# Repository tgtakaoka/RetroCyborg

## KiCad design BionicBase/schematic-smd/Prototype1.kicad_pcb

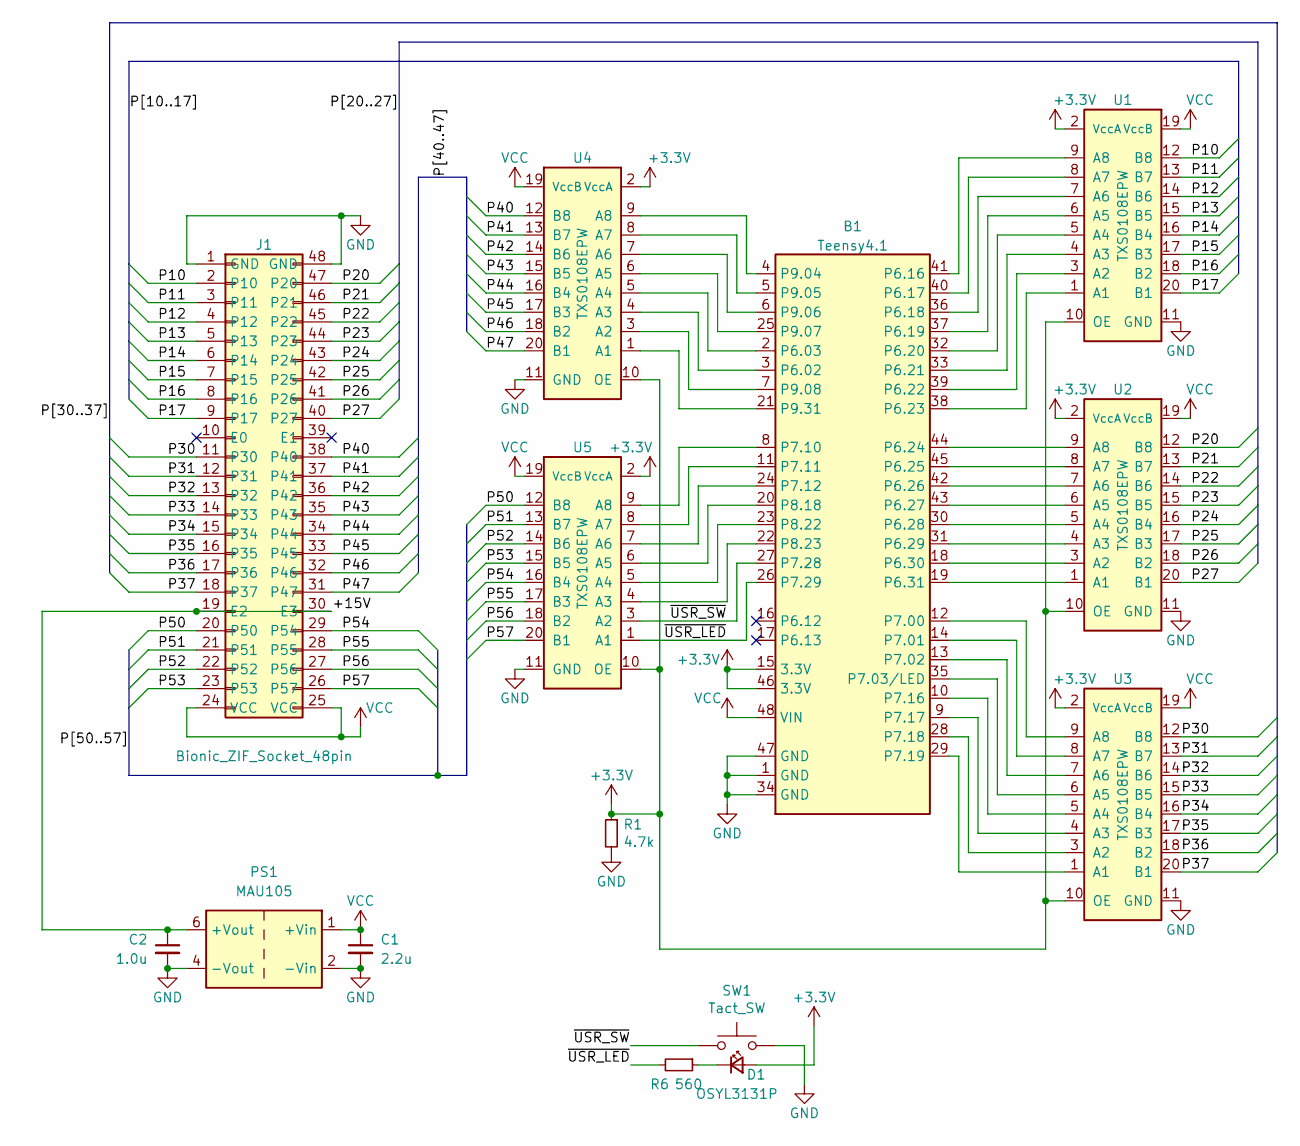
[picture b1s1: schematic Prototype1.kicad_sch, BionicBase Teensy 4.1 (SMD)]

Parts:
B1: Teensy4.1; DIP-48_W15.24mm
C1: 2.2u; C_0603_1608Metric_Pad1.08x0.95mm_HandSolder
C2: 1.0u; C_0603_1608Metric_Pad1.08x0.95mm_HandSolder
D1: OSYL3131P; LED_D3.0mm
J1: Bionic_ZIF_Socket_48pin; Aries_ZIF_socket_DIP-48-pin
PS1: MAU105; Converter_DCDC_Minmax_MAU100_THT
R1: 4.7k; R_Axial_DIN0204_L3.6mm_D1.6mm_P5.08mm_Horizontal
R6: 560; R_Axial_DIN0204_L3.6mm_D1.6mm_P5.08mm_Horizontal
SW1: Tact_SW; Tact_SW_6x6mm
U1, U2, U3, U4, U5: TXS0108EPW; TSSOP-20_4.4x6.5mm_P0.65mm

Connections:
+3.3V: B1.15 (3.3V), B1.46 (3.3V), D1.2 (A), R1.1, U1.2 (VccA), U1.10 (OE), U2.2 (VccA), U2.10 (OE), U3.2 (VccA), U3.10 (OE), U4.2 (VccA), U4.10 (OE), U5.2 (VccA), U5.10 (OE)
/+15V: C2.1, J1.19 (E2), J1.30 (E3), PS1.6 (+Vout)
/P10: J1.2 (P10), U1.12 (B8)
/P11: J1.3 (P11), U1.13 (B7)
/P12: J1.4 (P12), U1.14 (B6)
/P13: J1.5 (P13), U1.15 (B5)
/P14: J1.6 (P14), U1.16 (B4)
/P15: J1.7 (P15), U1.17 (B3)
/P16: J1.8 (P16), U1.18 (B2)
/P17: J1.9 (P17), U1.20 (B1)
/P20: J1.47 (P20), U2.12 (B8)
/P21: J1.46 (P21), U2.13 (B7)
/P22: J1.45 (P22), U2.14 (B6)
/P23: J1.44 (P23), U2.15 (B5)
/P24: J1.43 (P24), U2.16 (B4)
/P25: J1.42 (P25), U2.17 (B3)
/P26: J1.41 (P26), U2.18 (B2)
/P27: J1.40 (P27), U2.20 (B1)
/P30: J1.11 (P30), U3.12 (B8)
/P31: J1.12 (P31), U3.13 (B7)
/P32: J1.13 (P32), U3.14 (B6)
/P33: J1.14 (P33), U3.15 (B5)
/P34: J1.15 (P34), U3.16 (B4)
/P35: J1.16 (P35), U3.17 (B3)
/P36: J1.17 (P36), U3.18 (B2)
/P37: J1.18 (P37), U3.20 (B1)
/P40: J1.38 (P40), U4.12 (B8)
/P41: J1.37 (P41), U4.13 (B7)
/P42: J1.36 (P42), U4.14 (B6)
/P43: J1.35 (P43), U4.15 (B5)
/P44: J1.34 (P44), U4.16 (B4)
/P45: J1.33 (P45), U4.17 (B3)
/P46: J1.32 (P46), U4.18 (B2)
/P47: J1.31 (P47), U4.20 (B1)
/P50: J1.20 (P50), U5.12 (B8)
/P51: J1.21 (P51), U5.13 (B7)
/P52: J1.22 (P52), U5.14 (B6)
/P53: J1.23 (P53), U5.15 (B5)
/P54: J1.29 (P54), U5.16 (B4)
/P55: J1.28 (P55), U5.17 (B3)
/P56: J1.27 (P56), U5.18 (B2)
/P57: J1.26 (P57), U5.20 (B1)
/~USR_LED: B1.26 (P7.29), R6.2, U5.1 (A1)
/~USR_SW: B1.27 (P7.28), SW1.1, U5.3 (A2)
GND: B1.1 (GND), B1.34 (GND), B1.47 (GND), C1.2, C2.2, J1.1 (GND), J1.48 (GND), PS1.2 (-Vin), PS1.4 (-Vout), R1.2, SW1.2, U1.11 (GND), U2.11 (GND), U3.11 (GND), U4.11 (GND), U5.11 (GND)
unnamed: B1.3 (P6.02), U4.4 (A3)
unnamed: B1.2 (P6.03), U4.5 (A4)
unnamed: B1.41 (P6.16), U1.9 (A8)
unnamed: B1.40 (P6.17), U1.8 (A7)
unnamed: B1.36 (P6.18), U1.7 (A6)
unnamed: B1.37 (P6.19), U1.6 (A5)
unnamed: B1.32 (P6.20), U1.5 (A4)
unnamed: B1.33 (P6.21), U1.4 (A3)
unnamed: B1.39 (P6.22), U1.3 (A2)
unnamed: B1.38 (P6.23), U1.1 (A1)
unnamed: B1.44 (P6.24), U2.9 (A8)
unnamed: B1.45 (P6.25), U2.8 (A7)
unnamed: B1.42 (P6.26), U2.7 (A6)
unnamed: B1.43 (P6.27), U2.6 (A5)
unnamed: B1.30 (P6.28), U2.5 (A4)
unnamed: B1.31 (P6.29), U2.4 (A3)
unnamed: B1.18 (P6.30), U2.3 (A2)
unnamed: B1.19 (P6.31), U2.1 (A1)
unnamed: B1.12 (P7.00), U3.9 (A8)
unnamed: B1.14 (P7.01), U3.8 (A7)
unnamed: B1.13 (P7.02), U3.7 (A6)
unnamed: B1.35 (P7.03/LED), U3.6 (A5)
unnamed: B1.8 (P7.10), U5.9 (A8)
unnamed: B1.11 (P7.11), U5.8 (A7)
unnamed: B1.24 (P7.12), U5.7 (A6)
unnamed: B1.10 (P7.16), U3.5 (A4)
unnamed: B1.9 (P7.17), U3.4 (A3)
unnamed: B1.28 (P7.18), U3.3 (A2)
unnamed: B1.29 (P7.19), U3.1 (A1)
unnamed: B1.20 (P8.18), U5.6 (A5)
unnamed: B1.23 (P8.22), U5.5 (A4)
unnamed: B1.22 (P8.23), U5.4 (A3)
unnamed: B1.4 (P9.04), U4.9 (A8)
unnamed: B1.5 (P9.05), U4.8 (A7)
unnamed: B1.6 (P9.06), U4.7 (A6)
unnamed: B1.25 (P9.07), U4.6 (A5)
unnamed: B1.7 (P9.08), U4.3 (A2)
unnamed: B1.21 (P9.31), U4.1 (A1)
unnamed: D1.1 (K), R6.1
VCC: B1.48 (VIN), C1.1, J1.24 (VCC), J1.25 (VCC), PS1.1 (+Vin), U1.19 (VccB), U2.19 (VccB), U3.19 (VccB), U4.19 (VccB), U5.19 (VccB)

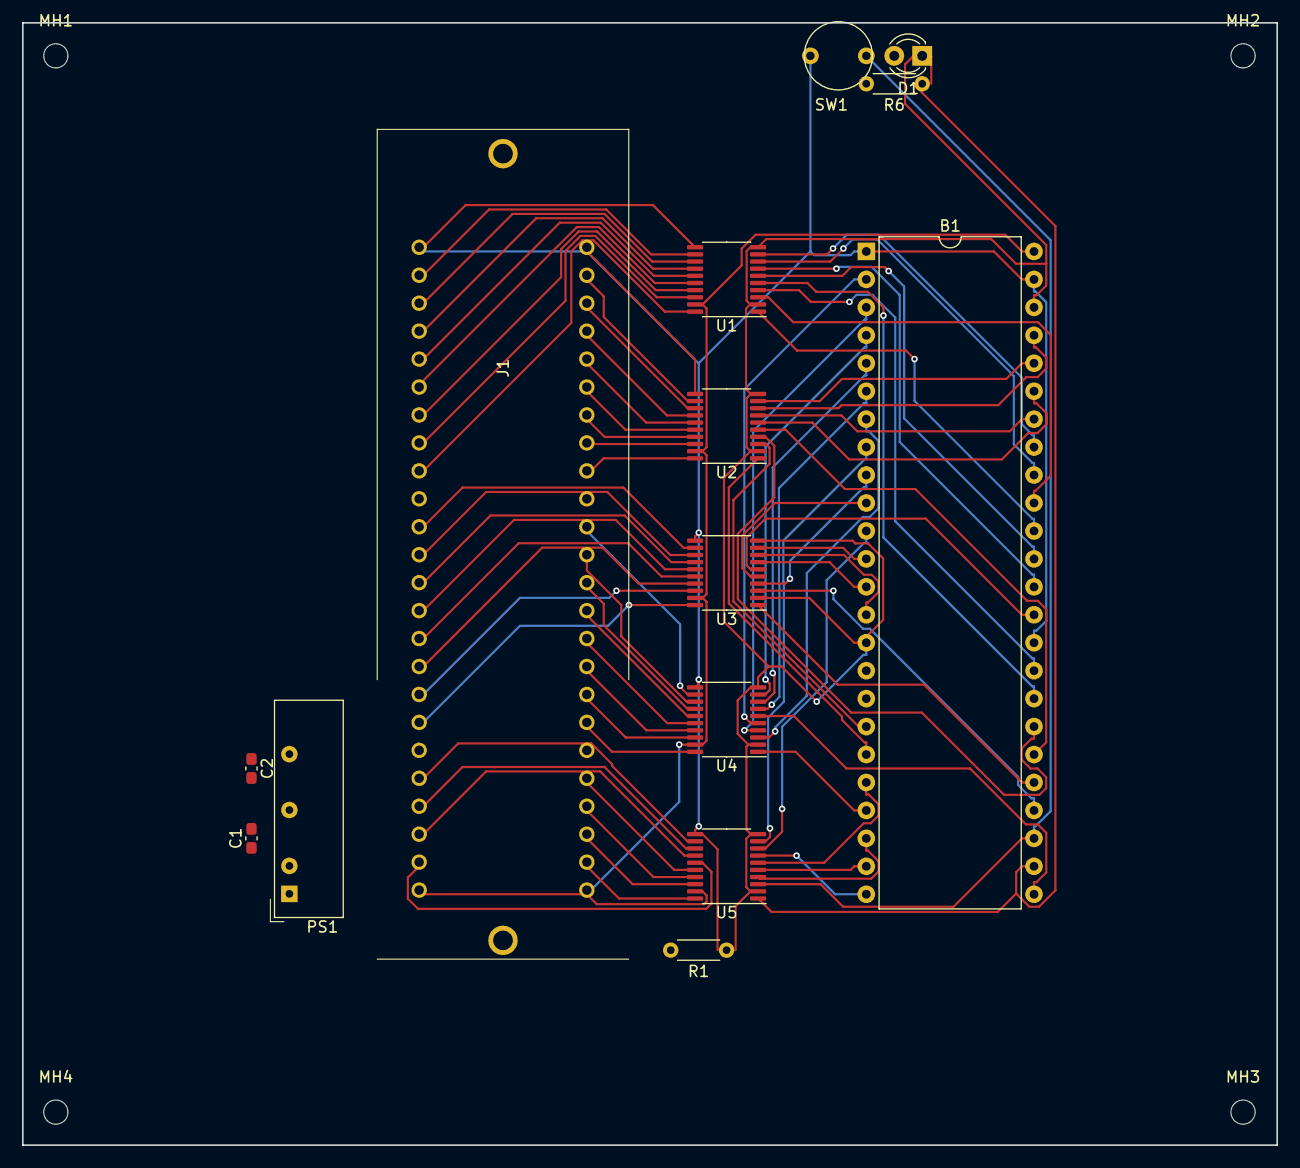
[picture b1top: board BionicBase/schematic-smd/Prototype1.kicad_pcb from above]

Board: 2 copper layers, 114.0 x 102.0 mm, 18 parts (0 on the bottom side), 85 nets.

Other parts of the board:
MH1, MH2, MH3, MH4: MountingHole_2.2mm_M2

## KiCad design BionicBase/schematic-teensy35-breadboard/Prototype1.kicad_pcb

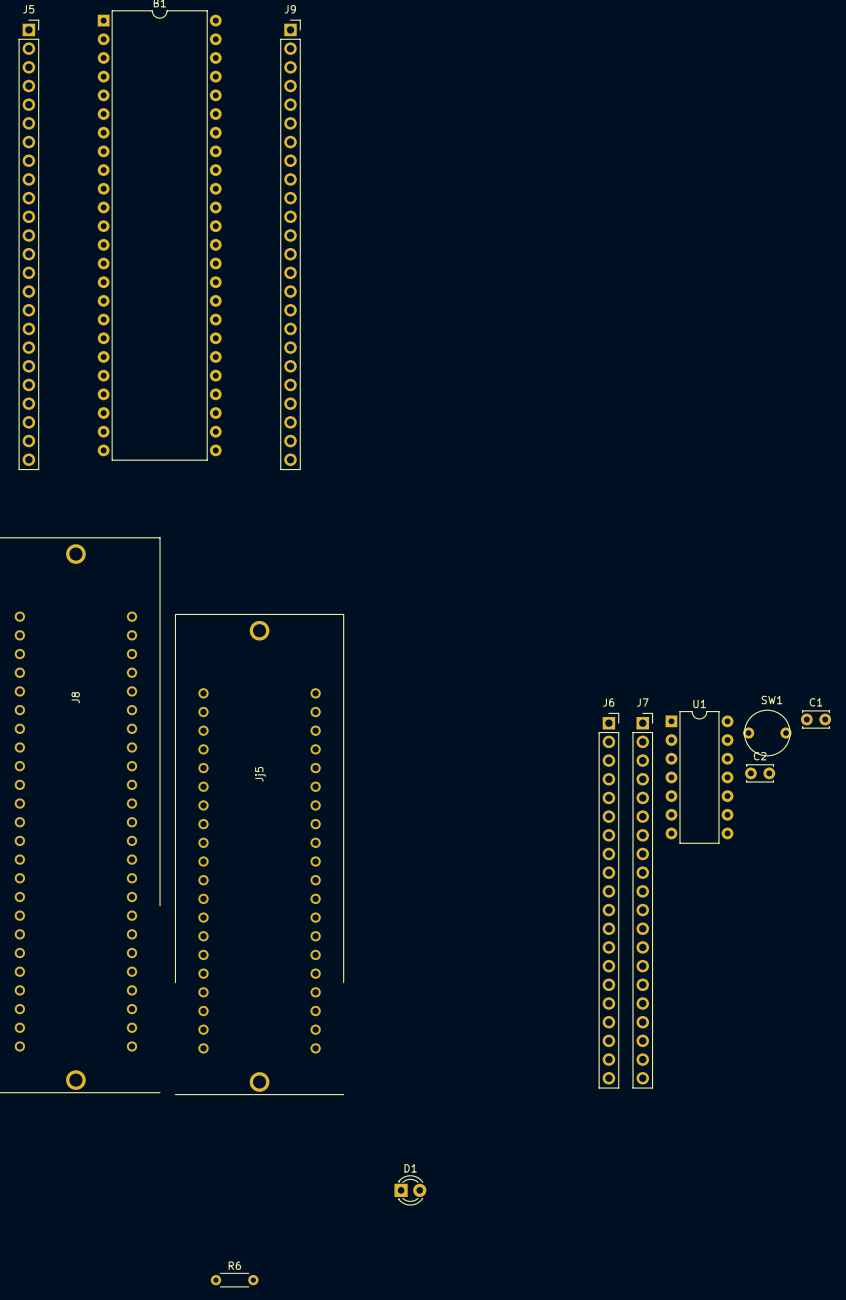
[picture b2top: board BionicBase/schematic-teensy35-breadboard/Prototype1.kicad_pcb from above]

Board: 2 copper layers, 13 parts (0 on the bottom side), 6 nets, no tracks yet.

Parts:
B1: Teensy3.5; DIP-48_W15.24mm
C1, C2: 0.1u; C_Disc_D3.4mm_W2.1mm_P2.50mm
D1: OSYL3131P; LED_D3.0mm
J5: Conn_01x24_T1-T24_30_53; PinSocket_1x24_P2.54mm_Vertical
J6: Conn_01x20_T1-T20_34_53; PinSocket_1x20_P2.54mm_Vertical
J7: Conn_01x20_T21-T40_34_53; PinSocket_1x20_P2.54mm_Vertical
J8: ZIF_Socket_48pin; Aries_ZIF_socket_DIP-48-pin
J9: Conn_01x24_T25-T48_30_53; PinSocket_1x24_P2.54mm_Vertical
Jj5: ZIF_Socket_40pin; Aries_ZIF_socket_DIP-40-pin
R6: 560; R_Axial_DIN0204_L3.6mm_D1.6mm_P5.08mm_Horizontal
SW1: Tact_SW; Tact_SW_6x6mm
U1: 74HCT126; DIP-14_W7.62mm

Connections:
+3V3: B1.15, B1.46
/PTB10: B1.23, SW1.1
/PTB11: B1.24, R6.2
GND: B1.1, B1.32, B1.34, C1.2, C2.2, SW1.2, U1.7
unnamed: D1.1, R6.1
VCC: B1.48, C1.1, C2.1, D1.2, U1.14

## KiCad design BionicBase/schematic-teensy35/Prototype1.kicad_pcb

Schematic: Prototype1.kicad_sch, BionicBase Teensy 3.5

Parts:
B1: Teensy3.5; DIP-48_W15.24mm
C1: 0.1u; C_Disc_D3.4mm_W2.1mm_P2.50mm
D1: OSYL3131P; LED_D3.0mm
J1: Bionic_ZIF_Socket_48pin; Aries_ZIF_socket_DIP-48-pin
R6: 560; R_Axial_DIN0204_L3.6mm_D1.6mm_P5.08mm_Horizontal
SW1: Tact_SW; Tact_SW_6x6mm

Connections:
+3V3: B1.15 (3.3V), B1.46 (3.3V)
/P10: B1.4 (PTD0), J1.2 (P10)
/P11: B1.36 (PTD1), J1.3 (P11)
/P12: B1.9 (PTD2), J1.4 (P12)
/P13: B1.10 (PTD3), J1.5 (P13)
/P14: B1.8 (PTD4), J1.6 (P14)
/P15: B1.42 (PTD5), J1.7 (P15)
/P16: B1.43 (PTD6), J1.8 (P16)
/P17: B1.7 (PTD7), J1.9 (P17)
/P20: B1.37 (PTC0), J1.47 (P20)
/P21: B1.44 (PTC1), J1.46 (P21)
/P22: B1.45 (PTC2), J1.45 (P22)
/P23: B1.11 (PTC3), J1.44 (P23)
/P24: B1.12 (PTC4), J1.43 (P24)
/P25: B1.35 (LED/PTC5), J1.42 (P25)
/P26: B1.13 (PTC6), J1.41 (P26)
/P27: B1.14 (PTC7), J1.40 (P27)
/P30: B1.27 (PTC8), J1.11 (P30)
/P31: B1.28 (PTC9), J1.12 (P31)
/P32: B1.29 (PTC10), J1.13 (P32)
/P33: B1.30 (PTC11), J1.14 (P33)
/P34: B1.5 (PTA12), J1.15 (P34)
/P35: B1.6 (PTA13), J1.16 (P35)
/P36: B1.18 (PTA14), J1.17 (P36)
/P37: B1.19 (PTA15), J1.18 (P37)
/P40: B1.38 (PTB0), J1.38 (P40)
/P41: B1.39 (PTB1), J1.37 (P41)
/P42: B1.41 (PTB2), J1.36 (P42)
/P43: B1.40 (PTB3), J1.35 (P43)
/P44: B1.2 (PTB16), J1.34 (P44)
/P45: B1.3 (PTB17), J1.33 (P45)
/P46: B1.21 (PTB18), J1.32 (P46)
/P47: B1.22 (PTB19), J1.31 (P47)
/P50: B1.25 (PTE24), J1.20 (P50)
/P51: B1.26 (PTE25), J1.21 (P51)
/P52: B1.16 (PTE26), J1.22 (P52)
/P53: B1.17 (PTA5), J1.23 (P53)
/P54: B1.20 (PTA16), J1.29 (P54)
/P55: B1.31 (PTA17), J1.28 (P55)
/P56: B1.23 (PTB10), J1.27 (P56), SW1.1
/P57: B1.24 (PTB11), J1.26 (P57), R6.2
GND: B1.1 (GND), B1.32 (AGND), B1.34 (GND), C1.2, J1.1 (GND), J1.48 (GND), SW1.2
unnamed: D1.1 (K), R6.1
VCC: B1.48 (VIN), C1.1, D1.2 (A), J1.24 (VCC), J1.25 (VCC)

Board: 2 copper layers, 10 parts (0 on the bottom side), 44 nets, no tracks yet.

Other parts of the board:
MH1, MH2, MH3, MH4: MountingHole_2.2mm_M2

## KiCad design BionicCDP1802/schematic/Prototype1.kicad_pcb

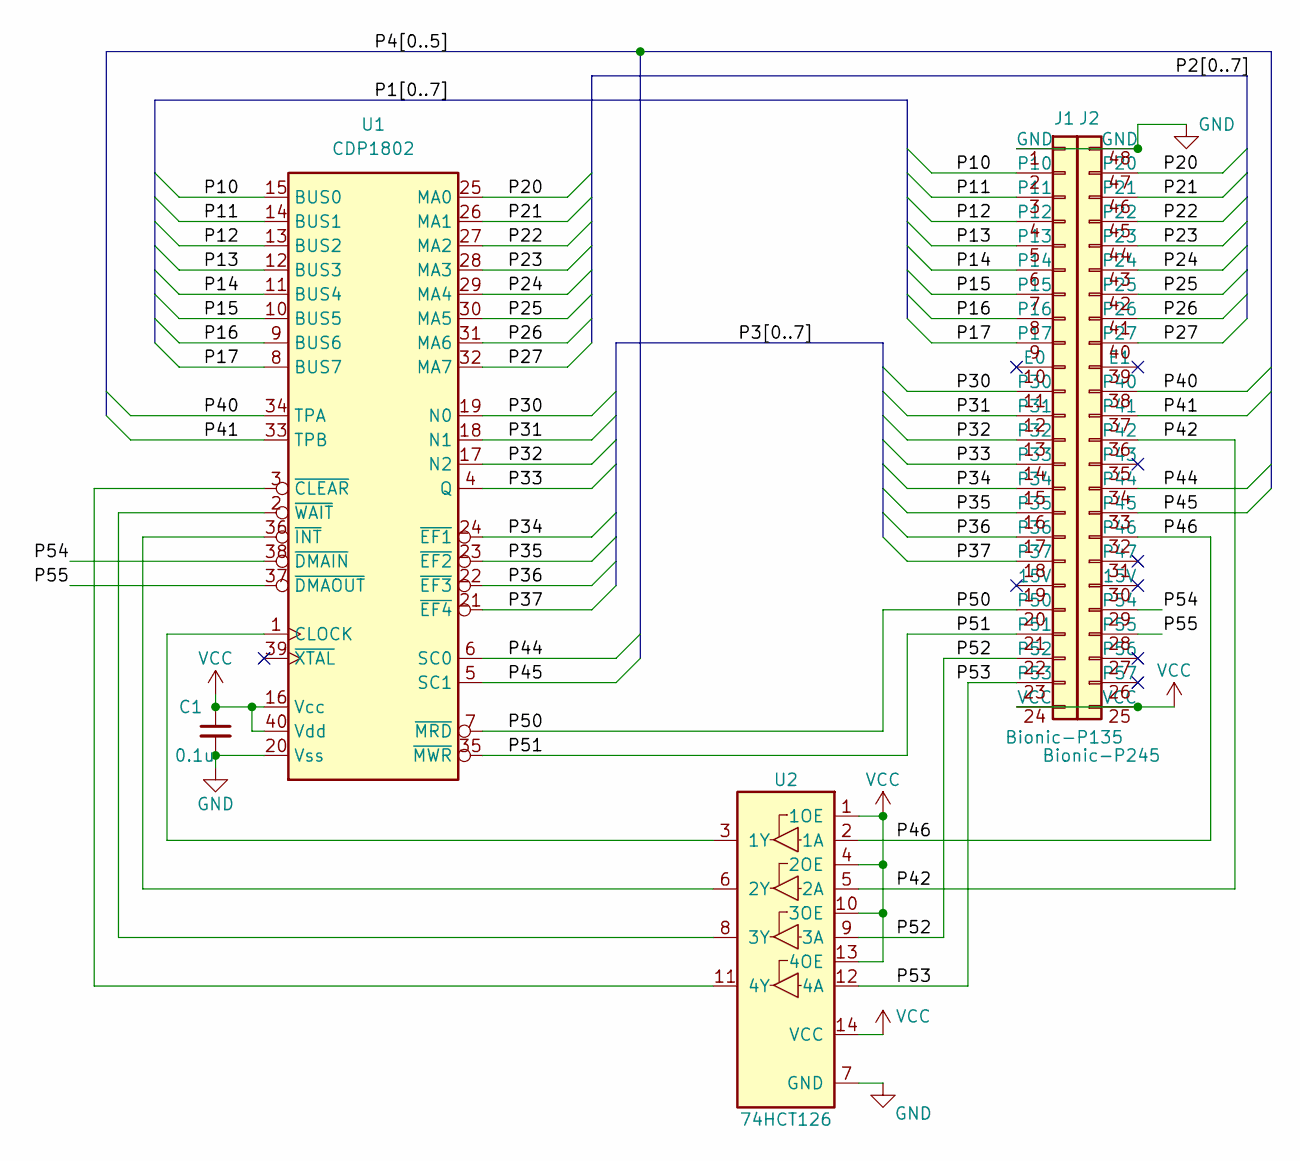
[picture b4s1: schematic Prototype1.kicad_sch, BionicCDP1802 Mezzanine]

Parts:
C1: 0.1u; C_Disc_D3.4mm_W2.1mm_P2.50mm
J1: Bionic-P135; Bionic-P135_Vertical
J2: Bionic-P245; Bionic-P245_Vertical
U1: CDP1802; DIP-40_W15.24mm
U2: 74HCT126; DIP-14_W7.62mm

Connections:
/P10: J1.2 (P10), U1.15 (BUS0)
/P11: J1.3 (P11), U1.14 (BUS1)
/P12: J1.4 (P12), U1.13 (BUS2)
/P13: J1.5 (P13), U1.12 (BUS3)
/P14: J1.6 (P14), U1.11 (BUS4)
/P15: J1.7 (P15), U1.10 (BUS5)
/P16: J1.8 (P16), U1.9 (BUS6)
/P17: J1.9 (P17), U1.8 (BUS7)
/P20: J2.47 (P20), U1.25 (MA0)
/P21: J2.46 (P21), U1.26 (MA1)
/P22: J2.45 (P22), U1.27 (MA2)
/P23: J2.44 (P23), U1.28 (MA3)
/P24: J2.43 (P24), U1.29 (MA4)
/P25: J2.42 (P25), U1.30 (MA5)
/P26: J2.41 (P26), U1.31 (MA6)
/P27: J2.40 (P27), U1.32 (MA7)
/P30: J1.11 (P30), U1.19 (N0)
/P31: J1.12 (P31), U1.18 (N1)
/P32: J1.13 (P32), U1.17 (N2)
/P33: J1.14 (P33), U1.4 (Q)
/P34: J1.15 (P34), U1.24 (~EF1)
/P35: J1.16 (P35), U1.23 (~EF2)
/P36: J1.17 (P36), U1.22 (~EF3)
/P37: J1.18 (P37), U1.21 (~EF4)
/P40: J2.38 (P40), U1.34 (TPA)
/P41: J2.37 (P41), U1.33 (TPB)
/P42: J2.36 (P42), U2.5 (2A)
/P44: J2.34 (P44), U1.6 (SC0)
/P45: J2.33 (P45), U1.5 (SC1)
/P46: J2.32 (P46), U2.2 (1A)
/P50: J1.20 (P50), U1.7 (~MRD)
/P51: J1.21 (P51), U1.35 (~MWR)
/P52: J1.22 (P52), U2.9 (3A)
/P53: J1.23 (P53), U2.12 (4A)
/P54: J2.29 (P54), U1.38 (~DMAIN)
/P55: J2.28 (P55), U1.37 (~DMAOUT)
GND: C1.2, J1.1 (GND), J2.48 (GND), U1.20 (Vss), U2.7 (GND)
unnamed: U1.1 (CLOCK), U2.3 (1Y)
unnamed: U1.3 (~CLEAR), U2.11 (4Y)
unnamed: U1.36 (~INT), U2.6 (2Y)
unnamed: U1.2 (~WAIT), U2.8 (3Y)
VCC: C1.1, J1.24 (VCC), J2.25 (VCC), U1.16 (Vcc), U1.40 (Vdd), U2.1 (1OE), U2.4 (2OE), U2.10 (3OE), U2.13 (4OE), U2.14 (VCC)

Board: 2 copper layers, 9 parts (0 on the bottom side), 42 nets, no tracks yet.

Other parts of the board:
MH1, MH2, MH3, MH4: MountingHole_3.2mm_M3

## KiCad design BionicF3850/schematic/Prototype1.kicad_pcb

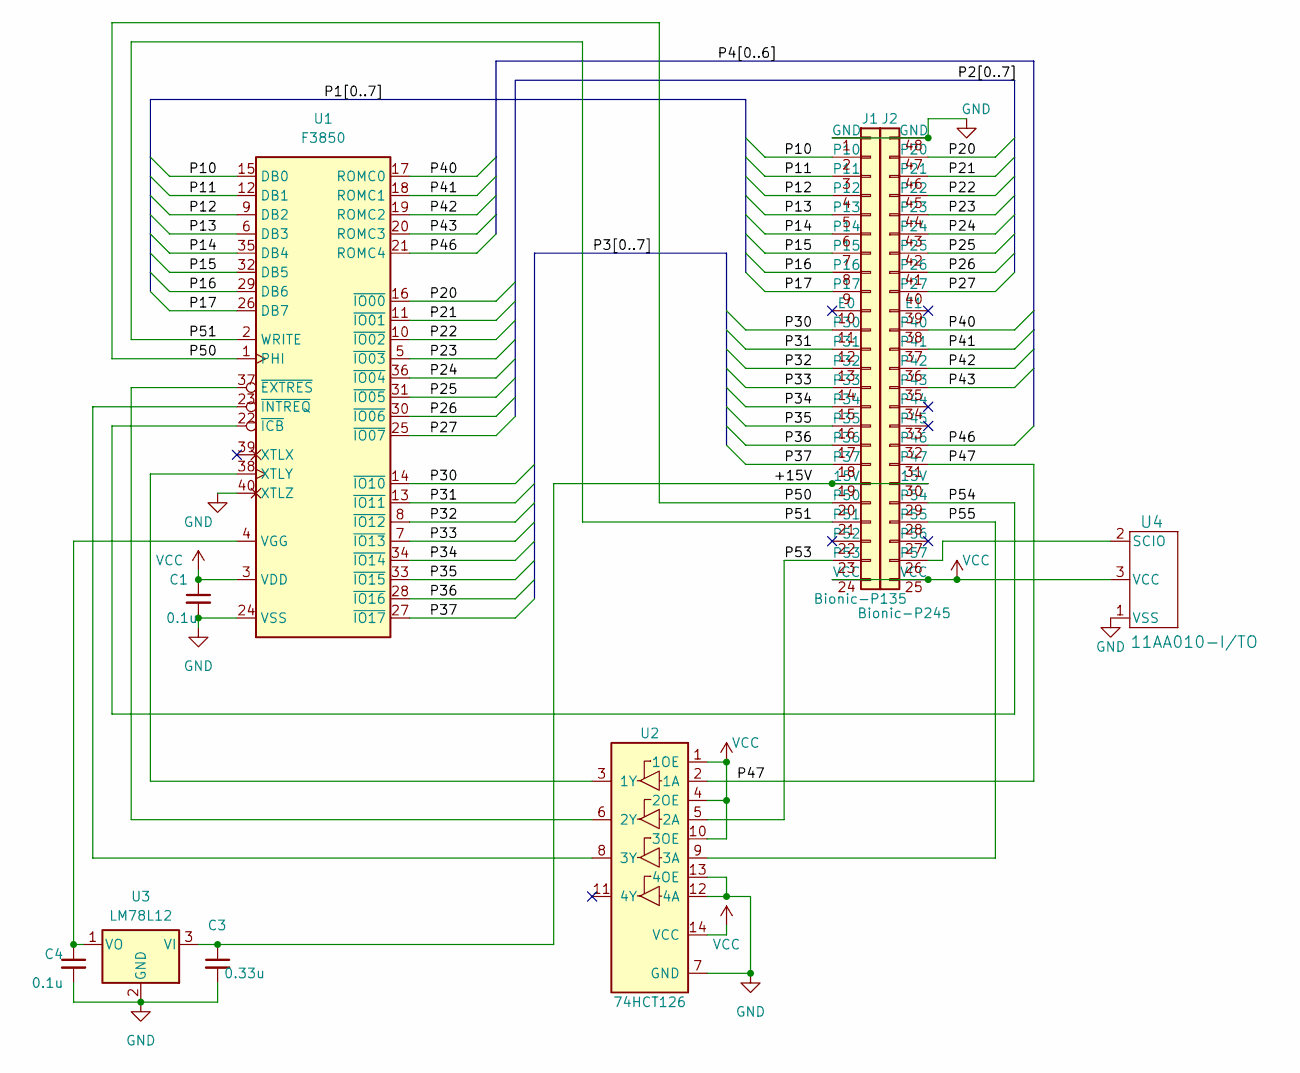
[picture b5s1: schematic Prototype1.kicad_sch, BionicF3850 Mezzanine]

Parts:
C1, C4: 0.1u; C_Disc_D3.4mm_W2.1mm_P2.50mm
C3: 0.33u; C_Disc_D3.4mm_W2.1mm_P2.50mm
J1: Bionic-P135; Bionic-P135_Vertical
J2: Bionic-P245; Bionic-P245_Vertical
U1: F3850; DIP-40_W15.24mm_Socket
U2: 74HCT126; DIP-14_W7.62mm_Socket
U3: LM78L12; TO-92_Inline
U4: 11AA010-I/TO; TO-92_MC_MCH

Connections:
/+15V: C3.1, J1.19 (15V), J2.30 (15V), U3.3 (VI)
/P10: J1.2 (P10), U1.15 (DB0)
/P11: J1.3 (P11), U1.12 (DB1)
/P12: J1.4 (P12), U1.9 (DB2)
/P13: J1.5 (P13), U1.6 (DB3)
/P14: J1.6 (P14), U1.35 (DB4)
/P15: J1.7 (P15), U1.32 (DB5)
/P16: J1.8 (P16), U1.29 (DB6)
/P17: J1.9 (P17), U1.26 (DB7)
/P20: J2.47 (P20), U1.16 (~IO00)
/P21: J2.46 (P21), U1.11 (~IO01)
/P22: J2.45 (P22), U1.10 (~IO02)
/P23: J2.44 (P23), U1.5 (~IO03)
/P24: J2.43 (P24), U1.36 (~IO04)
/P25: J2.42 (P25), U1.31 (~IO05)
/P26: J2.41 (P26), U1.30 (~IO06)
/P27: J2.40 (P27), U1.25 (~IO07)
/P30: J1.11 (P30), U1.14 (~IO10)
/P31: J1.12 (P31), U1.13 (~IO11)
/P32: J1.13 (P32), U1.8 (~IO12)
/P33: J1.14 (P33), U1.7 (~IO13)
/P34: J1.15 (P34), U1.34 (~IO14)
/P35: J1.16 (P35), U1.33 (~IO15)
/P36: J1.17 (P36), U1.28 (~IO16)
/P37: J1.18 (P37), U1.27 (~IO17)
/P40: J2.38 (P40), U1.17 (ROMC0)
/P41: J2.37 (P41), U1.18 (ROMC1)
/P42: J2.36 (P42), U1.19 (ROMC2)
/P43: J2.35 (P43), U1.20 (ROMC3)
/P46: J2.32 (P46), U1.21 (ROMC4)
/P47: J2.31 (P47), U2.2 (1A)
/P50: J1.20 (P50), U1.1 (PHI)
/P51: J1.21 (P51), U1.2 (WRITE)
/P53: J1.23 (P53), U2.5 (2A)
/P54: J2.29 (P54), U1.22 (~ICB)
/P55: J2.28 (P55), U2.9 (3A)
GND: C1.2, C3.2, C4.2, J1.1 (GND), J2.48 (GND), U1.24 (VSS), U1.40 (XTLZ), U2.7 (GND), U2.12 (4A), U2.13 (4OE), U3.2 (GND), U4.1 (VSS)
unnamed: J2.26 (P57), U4.2 (SCIO)
unnamed: C4.1, U1.4 (VGG), U3.1 (VO)
unnamed: U1.38 (XTLY), U2.3 (1Y)
unnamed: U1.37 (~EXTRES), U2.6 (2Y)
unnamed: U1.23 (~INTREQ), U2.8 (3Y)
VCC: C1.1, J1.24 (VCC), J2.25 (VCC), U1.3 (VDD), U2.1 (1OE), U2.4 (2OE), U2.10 (3OE), U2.14 (VCC), U4.3 (VCC)

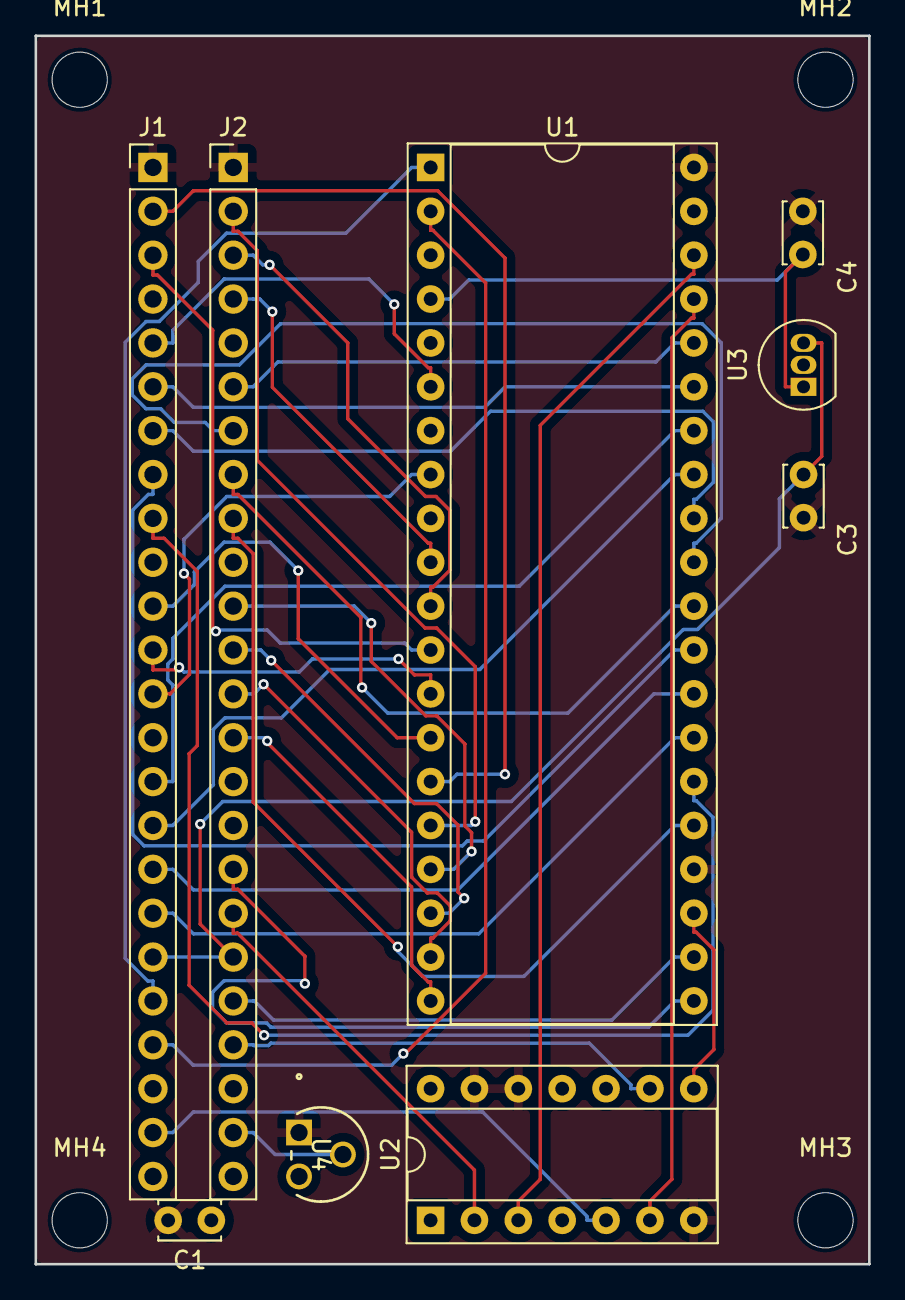
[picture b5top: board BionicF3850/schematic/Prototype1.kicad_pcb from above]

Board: 2 copper layers, 48.3 x 71.1 mm, 13 parts (0 on the bottom side), 43 nets.

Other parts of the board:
MH1, MH2, MH3, MH4: MountingHole_3.2mm_M3

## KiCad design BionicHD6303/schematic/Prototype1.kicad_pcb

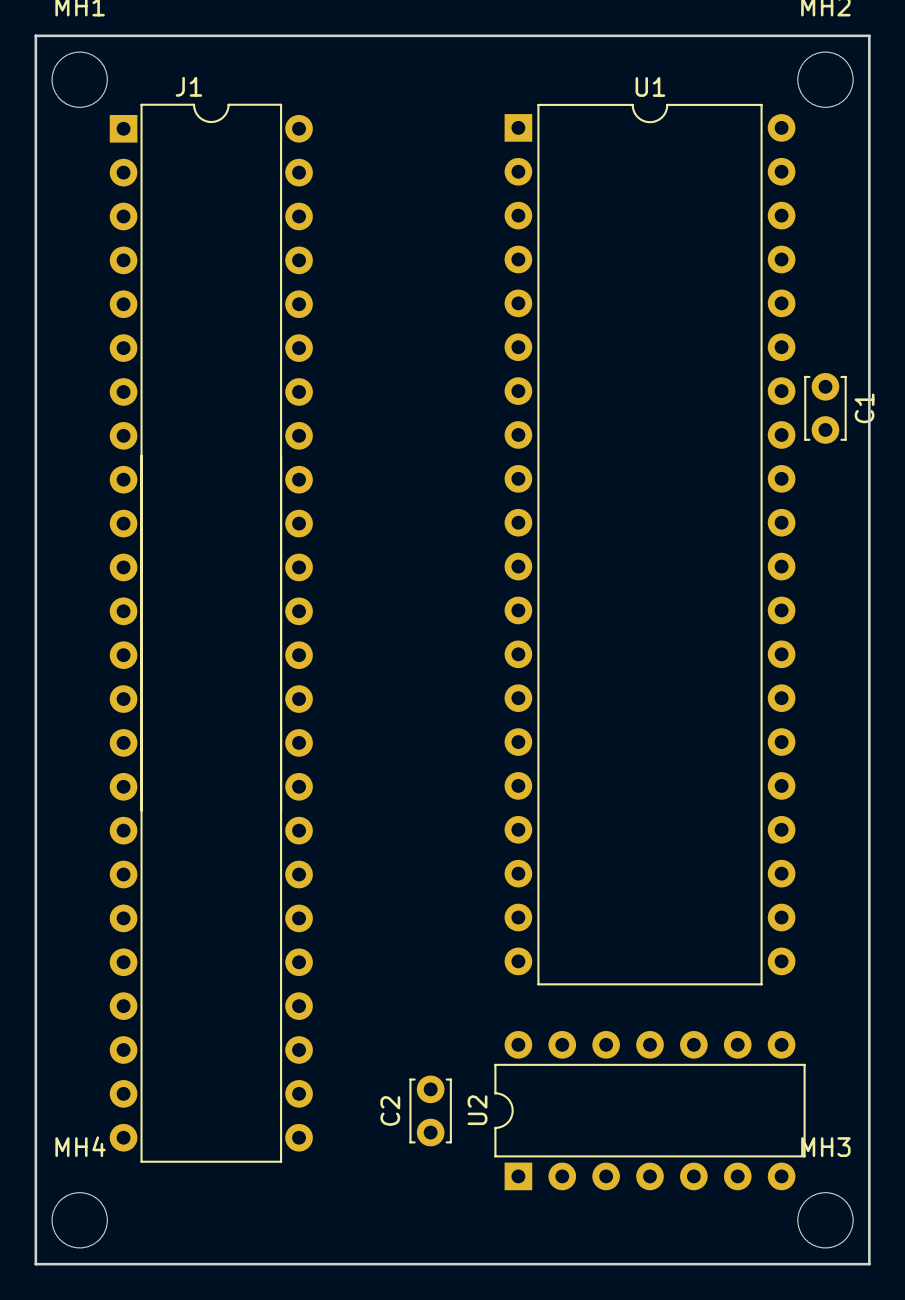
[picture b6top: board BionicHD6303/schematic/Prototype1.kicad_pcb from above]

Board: 2 copper layers, 48.3 x 71.1 mm, 9 parts (0 on the bottom side), 30 nets, no tracks yet.

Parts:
C1, C2: 0.1u; C_Disc_D3.4mm_W2.1mm_P2.50mm
J1: BionicConnector; DIP-48_W10.16mm
MH1, MH2, MH3, MH4: MountingHole_3.2mm_M3
U1: HD6303R1P; DIP-40_W15.24mm
U2: 74HCT126; DIP-14_W7.62mm

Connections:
/#RESET: U1.6, U2.3
/P10: J1.2, U1.37
/P11: J1.3, U1.36
/P12: J1.4, U1.35
/P13: J1.5, U1.34
/P14: J1.6, U1.33
/P15: J1.7, U1.32
/P16: J1.8, U1.31
/P17: J1.9, U1.30
/P20: J1.11, U1.29
/P21: J1.12, U1.28
/P22: J1.13, U1.27
/P23: J1.14, U1.26
/P24: J1.15, U1.25
/P25: J1.16, U1.24
/P26: J1.17, U1.23
/P27: J1.18, U1.22
/P34: J1.42, U1.8
/P35: J1.35, J1.41, U1.4, U1.9
/P36: J1.40, U1.10
/P40: J1.38, U1.39
/P41: J1.37, U1.38
/P42: J1.36, U1.5
/P44: J1.34, U1.12
/P45: J1.33, U1.11
/P46: J1.32, U1.3
/P47: J1.31, U1.40
/P53: J1.23, U2.2
GND: C1.2, C2.2, J1.1, J1.48, U1.1, U2.4, U2.5, U2.7, U2.9, U2.10, U2.12, U2.13
VCC: C1.1, C2.1, J1.24, J1.25, U1.7, U1.21, U2.1, U2.14

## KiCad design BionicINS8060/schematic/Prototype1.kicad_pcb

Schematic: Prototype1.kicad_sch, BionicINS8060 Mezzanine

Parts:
C1: 0.1u; C_Disc_D3.4mm_W2.1mm_P2.50mm
J1: BionicConnector; DIP-48_W7.62mm
U1: INS8060; DIP-40_W15.24mm
U2: 74HCT126; DIP-14_W7.62mm

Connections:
/P10: J1.2 (P10), U1.16 (DB0)
/P11: J1.3 (P11), U1.15 (DB1)
/P12: J1.4 (P12), U1.14 (DB2)
/P13: J1.5 (P13), U1.13 (DB3)
/P14: J1.6 (P14), U1.12 (DB4)
/P15: J1.7 (P15), U1.11 (DB5)
/P16: J1.8 (P16), U1.10 (DB6)
/P17: J1.9 (P17), U1.9 (DB7)
/P20: J1.47 (P20), U1.25 (AD00)
/P21: J1.46 (P21), U1.26 (AD01)
/P22: J1.45 (P22), U1.27 (AD02)
/P23: J1.44 (P23), U1.28 (AD03)
/P24: J1.43 (P24), U1.29 (AD04)
/P25: J1.42 (P25), U1.30 (AD05)
/P26: J1.41 (P26), U1.31 (AD06)
/P27: J1.40 (P27), U1.32 (AD07)
/P30: J1.11 (P30), U1.33 (AD08)
/P31: J1.12 (P31), U1.34 (AD09)
/P32: J1.13 (P32), U1.35 (AD10)
/P33: J1.14 (P33), U1.36 (AD11)
/P34: J1.15 (P34), U1.19 (FLAG0)
/P35: J1.16 (P35), U1.21 (FLAG1)
/P36: J1.17 (P36), U1.22 (FLAG2)
/P40: J1.38 (P40), U1.8 (CONT)
/P41: J1.37 (P41), U1.1 (~WDS)
/P42: J1.36 (P42), U1.18 (SENSEB)
/P43: J1.35 (P43), U1.17 (SENSEA)
/P44: J1.34 (P44), U1.23 (SOUT)
/P45: J1.33 (P45), U1.24 (SIN)
/P46: J1.32 (P46), U2.2 (1A)
/P47: J1.31 (P47), U1.5 (~BREQ)
/P50: J1.20 (P50), U1.2 (~RDS)
/P51: J1.21 (P51), U1.39 (~ADS)
/P52: J1.22 (P52), U1.6 (~HOLD)
/P53: J1.23 (P53), U1.7 (~RST)
/P54: J1.29 (P54), U1.3 (~ENIN)
/P55: J1.28 (P55), U1.4 (~ENOUT)
GND: C1.2, J1.1 (GND), J1.48 (GND), U1.20 (GND), U2.4 (2OE), U2.5 (2A), U2.7 (GND), U2.9 (3A), U2.10 (3OE), U2.12 (4A), U2.13 (4OE)
unnamed: U1.37 (XIN), U2.3 (1Y)
VCC: C1.1, J1.24 (VCC), J1.25 (VCC), U1.40 (VCC), U2.1 (1OE), U2.14 (VCC)

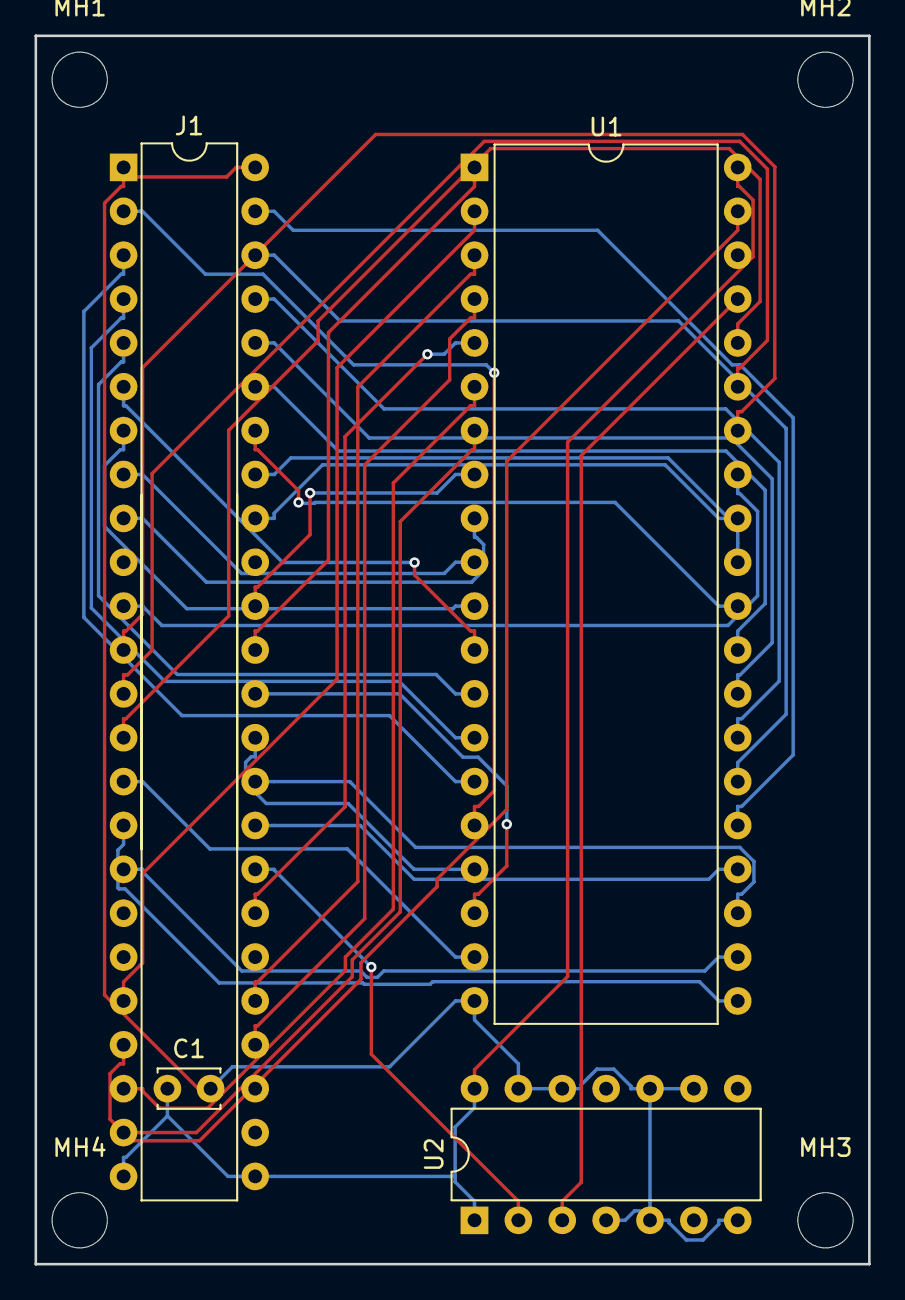
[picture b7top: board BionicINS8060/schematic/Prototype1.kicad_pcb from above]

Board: 2 copper layers, 48.3 x 71.1 mm, 8 parts (0 on the bottom side), 40 nets.

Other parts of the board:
MH1, MH2, MH3, MH4: MountingHole_3.2mm_M3
